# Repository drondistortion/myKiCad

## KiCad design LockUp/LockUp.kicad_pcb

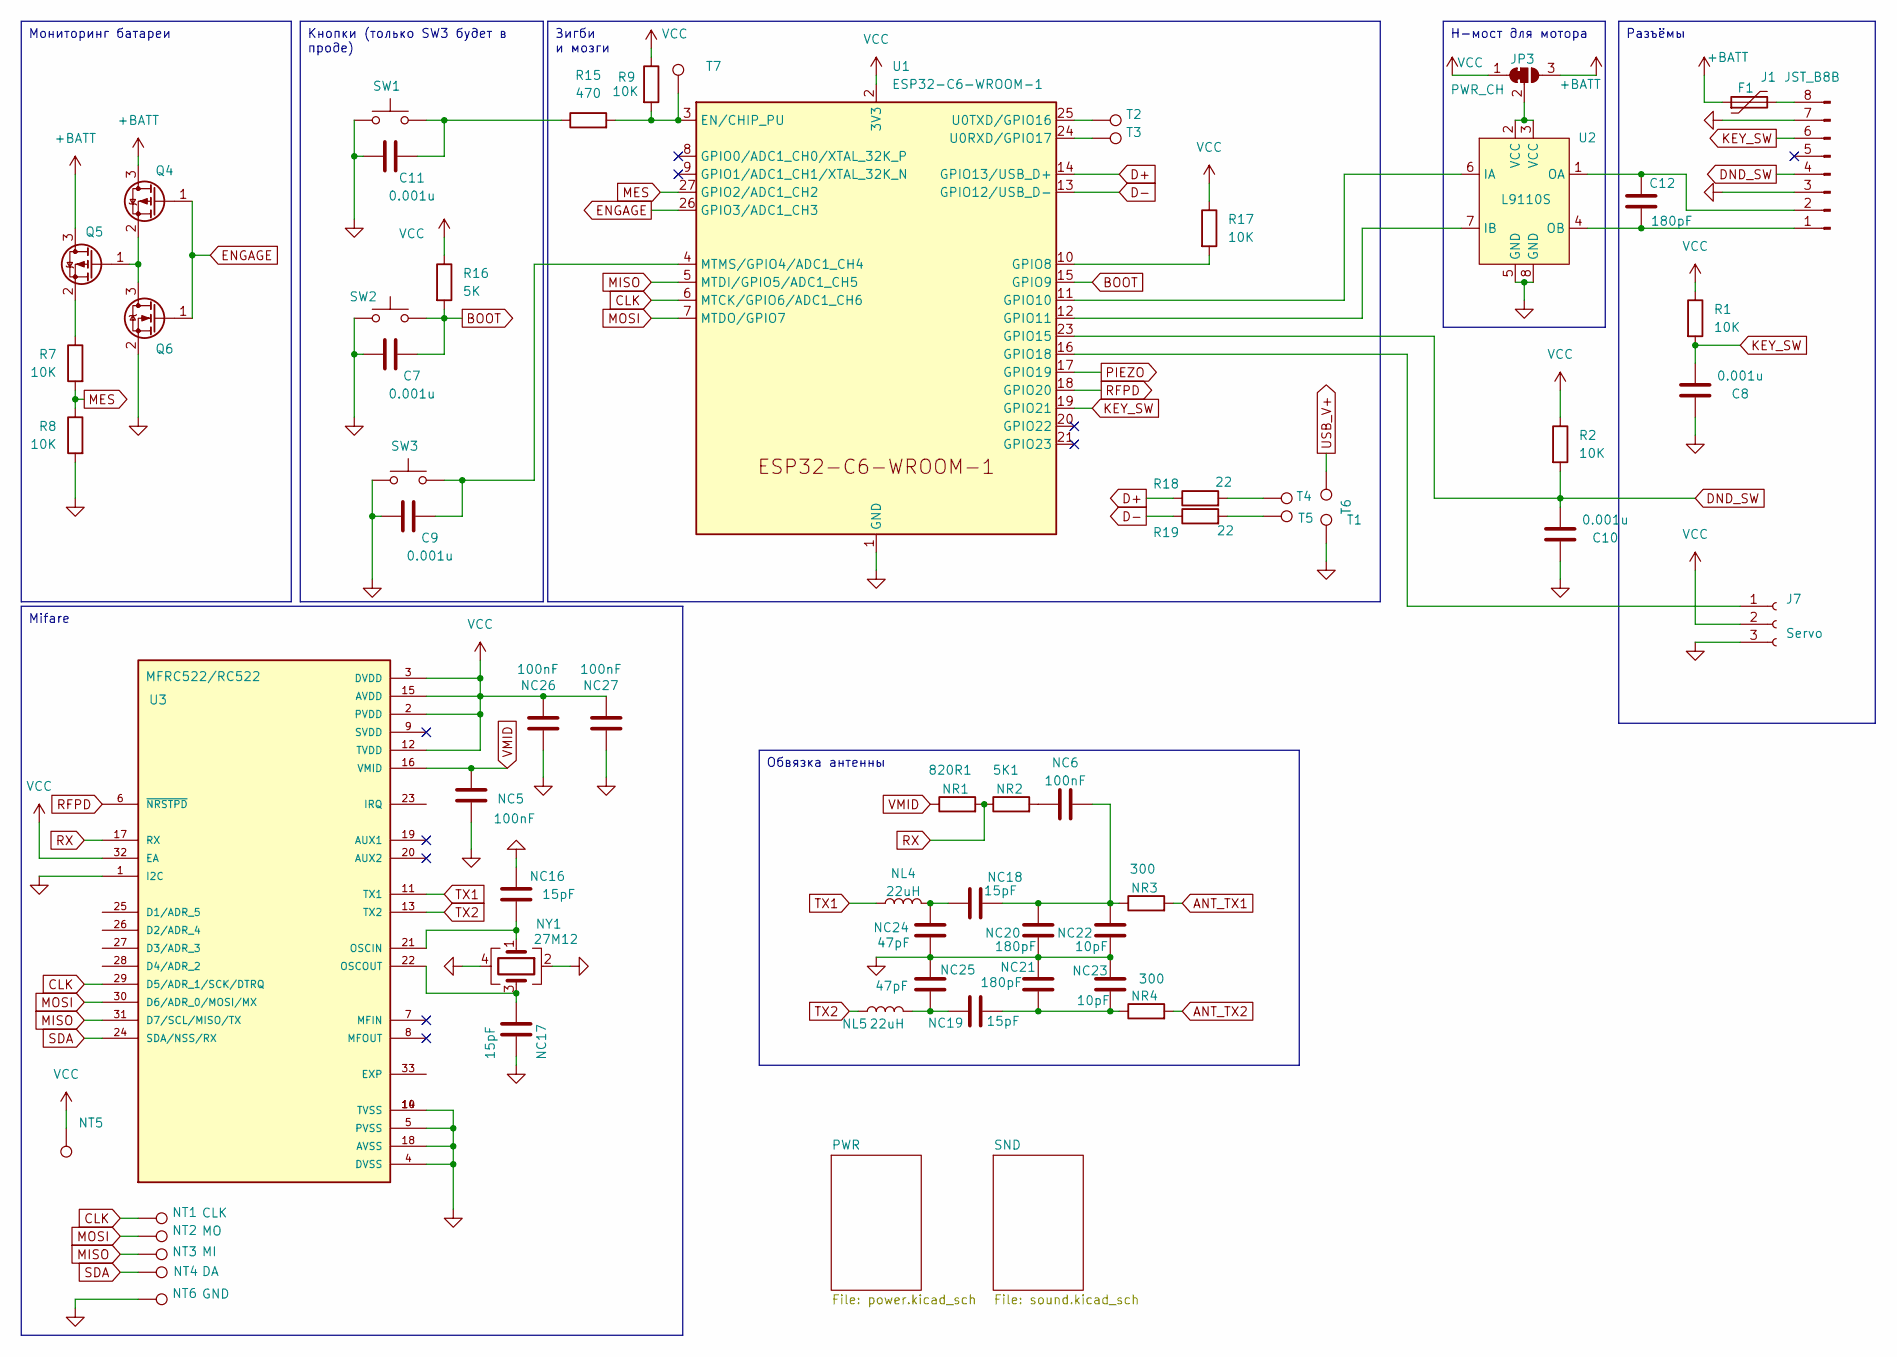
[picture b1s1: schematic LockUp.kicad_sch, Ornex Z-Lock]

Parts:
C7, C8, C9, C10, C11: 0.001u; C_0805_2012Metric_Pad1.18x1.45mm_HandSolder
C12: 180pF; C_0805_2012Metric_Pad1.18x1.45mm_HandSolder
F1: Polyfuse; Fuse_1206_3216Metric_Pad1.42x1.75mm_HandSolder
J1: JST_B8B; JST_PH_B8B-PH-SM4-TB_1x08-1MP_P2.00mm_Vertical
J7: Servo; Molex_PicoBlade_53398-0371_1x03-1MP_P1.25mm_Vertical
JP3: PWR_CH; SolderJumper-3_P1.3mm_Bridged12_RoundedPad1.0x1.5mm
NC5, NC6, NC26, NC27: 100nF; C_0805_2012Metric_Pad1.18x1.45mm_HandSolder
NC16, NC17, NC18, NC19: 15pF; C_0805_2012Metric_Pad1.18x1.45mm_HandSolder
NC20, NC21: 180pF; C_0805_2012Metric_Pad1.18x1.45mm_HandSolder
NC22, NC23: 10pF; C_0805_2012Metric_Pad1.18x1.45mm_HandSolder
NC24, NC25: 47pF; C_0805_2012Metric_Pad1.18x1.45mm_HandSolder
NL4, NL5: 22uH; L_0805_2012Metric_Pad1.15x1.40mm_HandSolder
NR1: 820R1; R_0805_2012Metric_Pad1.20x1.40mm_HandSolder
NR2: 5K1; R_0805_2012Metric_Pad1.20x1.40mm_HandSolder
NR3, NR4: 300; R_0805_2012Metric_Pad1.20x1.40mm_HandSolder
NT1: CLK; TestPoint_Pad_1.0x1.0mm
NT2: MO; TestPoint_Pad_1.0x1.0mm
NT3: MI; TestPoint_Pad_1.0x1.0mm
NT4: DA; TestPoint_Pad_1.0x1.0mm
NT5: 3V3; TestPoint_Pad_1.0x1.0mm
NT6: GND; TestPoint_Pad_1.0x1.0mm
NY1: 27M12; Crystal_SMD_3225-4Pin_3.2x2.5mm_HandSoldering
Q4, Q5: Si2323; SOT-23
Q6: AO3400A; SOT-23
R1, R2, R7, R8, R9, R17: 10K; R_0805_2012Metric_Pad1.20x1.40mm_HandSolder
R15: 470; R_0805_2012Metric_Pad1.20x1.40mm_HandSolder
R16: 5K; R_0805_2012Metric_Pad1.20x1.40mm_HandSolder
R18, R19: 22; R_0805_2012Metric_Pad1.20x1.40mm_HandSolder
SW1: RST; SW_Push_1P1T_XKB_TS-1187A
SW2: BOOT; SW_Push_1P1T_XKB_TS-1187A
SW3: NT_RST; SW_Push_1P1T_XKB_TS-1187A
T1: GND; TestPoint_THTPad_D0.6mm_Drill0.3mm
T2: TX; TestPoint_Pad_D1.0mm
T3: RX; TestPoint_Pad_D1.0mm
T4: D+; TestPoint_THTPad_D0.6mm_Drill0.3mm
T5: D-; TestPoint_THTPad_D0.6mm_Drill0.3mm
T6: VCC; TestPoint_THTPad_D0.6mm_Drill0.3mm
T7: RES; TestPoint_Pad_D1.0mm
U1: ESP32-C6-WROOM-1
U2: L9110S; SOP-8_3.9x4.9mm_P1.27mm
U3: MFRC522/RC522; HVQFN-32-1EP_5x5mm_P0.5mm_EP3.1x3.1mm; PARTREV 3.9

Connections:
+BATT: F1.1, JP3.3 (B), Q4.3 (D), Q5.3 (D); also elsewhere on the board
ANT_TX1: NR3.2
ANT_TX2: NR4.2
BOOT: C7.2, R16.2, SW2.2, U1.15 (GPIO9)
CLK: NT1.1, U1.6 (MTCK/GPIO6/ADC1_CH6), U3.29 (D5/ADR_1/SCK/DTRQ)
D+: R18.1, U1.14 (GPIO13/USB_D+)
D-: R19.1, U1.13 (GPIO12/USB_D-)
DND_SW: C10.2, J1.4, R2.2, U1.23 (GPIO15)
ENGAGE: Q4.1 (G), Q6.1 (G), U1.26 (GPIO3/ADC1_CH3)
GND: C7.1, C8.1, C9.1, C10.1, C11.1, J1.3, J1.7, J7.3, NC5.2, NC16.2, NC17.2, NC20.2, NC21.1, NC22.2, NC23.1, NC24.2, NC25.1, NC26.1, NC27.2, NT6.1, NY1.2, NY1.4, Q6.2 (S), R8.2, SW1.1, SW2.1, SW3.1, T1.1, U1.1 (GND), U1.28 (GND), U1.29 (GND), U2.5 (GND), U2.8 (GND), U3.1 (I2C), U3.4 (DVSS), U3.5 (PVSS), U3.10 (TVSS), U3.14 (TVSS), U3.18 (AVSS); also elsewhere on the board
KEY_SW: C8.2, J1.6, R1.2, U1.19 (GPIO21)
MES: R7.2, R8.1, U1.27 (GPIO2/ADC1_CH2)
MISO: NT3.1, U1.5 (MTDI/GPIO5/ADC1_CH5), U3.31 (D7/SCL/MISO/TX)
MOSI: NT2.1, U1.7 (MTDO/GPIO7), U3.30 (D6/ADR_0/MOSI/MX)
unnamed: C11.2, R15.1, SW1.2
unnamed: C12.2, J1.1, U2.4 (OB)
unnamed: C12.1, J1.2, U2.1 (OA)
unnamed: F1.2, J1.8
unnamed: J7.1, U1.16 (GPIO18)
unnamed: JP3.2 (C), U2.2 (VCC), U2.3 (VCC)
unnamed: NC6.1, NR2.2
unnamed: NC18.1, NC24.1, NL4.2
unnamed: NC6.2, NC18.2, NC20.1, NC22.1, NR3.1
unnamed: NC19.1, NC25.2, NL5.2
unnamed: NC19.2, NC21.2, NC23.2, NR4.1
unnamed: Q4.2 (S), Q5.1 (G), Q6.3 (D)
unnamed: Q5.2 (S), R7.1
unnamed: R18.2, T4.1
unnamed: R19.2, T5.1
unnamed: R9.2, R15.2, T7.1, U1.3 (EN/CHIP_PU)
unnamed: R17.2, U1.10 (GPIO8)
unnamed: U1.11 (GPIO10), U2.6 (IA)
unnamed: U1.12 (GPIO11), U2.7 (IB)
unnamed: C9.2, SW3.2, U1.4 (MTMS/GPIO4/ADC1_CH4)
unnamed: T3.1, U1.24 (U0RXD/GPIO17)
unnamed: T2.1, U1.25 (U0TXD/GPIO16)
unnamed: NC16.1, NY1.1, U3.21 (OSCIN)
unnamed: NC17.1, NY1.3, U3.22 (OSCOUT)
PIEZO: U1.17 (GPIO19); also elsewhere on the board
RFPD: U1.18 (GPIO20), U3.6 (~NRSTPD)
RX: NR1.2, NR2.1, U3.17 (RX)
SDA: NT4.1, U3.24 (SDA/NSS/RX)
TX1: NL4.1, U3.11 (TX1)
TX2: NL5.1, U3.13 (TX2)
USB_V+: T6.1; also elsewhere on the board
VCC: J7.2, JP3.1 (A), NC26.2, NC27.1, NT5.1, R1.1, R2.1, R9.1, R16.1, R17.1, U1.2 (3V3), U3.2 (PVDD), U3.3 (DVDD), U3.12 (TVDD), U3.15 (AVDD), U3.32 (EA); also elsewhere on the board
VMID: NC5.1, NR1.1, U3.16 (VMID)

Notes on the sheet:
Мониторинг батареи
Кнопки (только SW3 будет в проде)
Mifare
Н-мост для мотора
Разъёмы
Обвязка антенны
Зигби и мозги

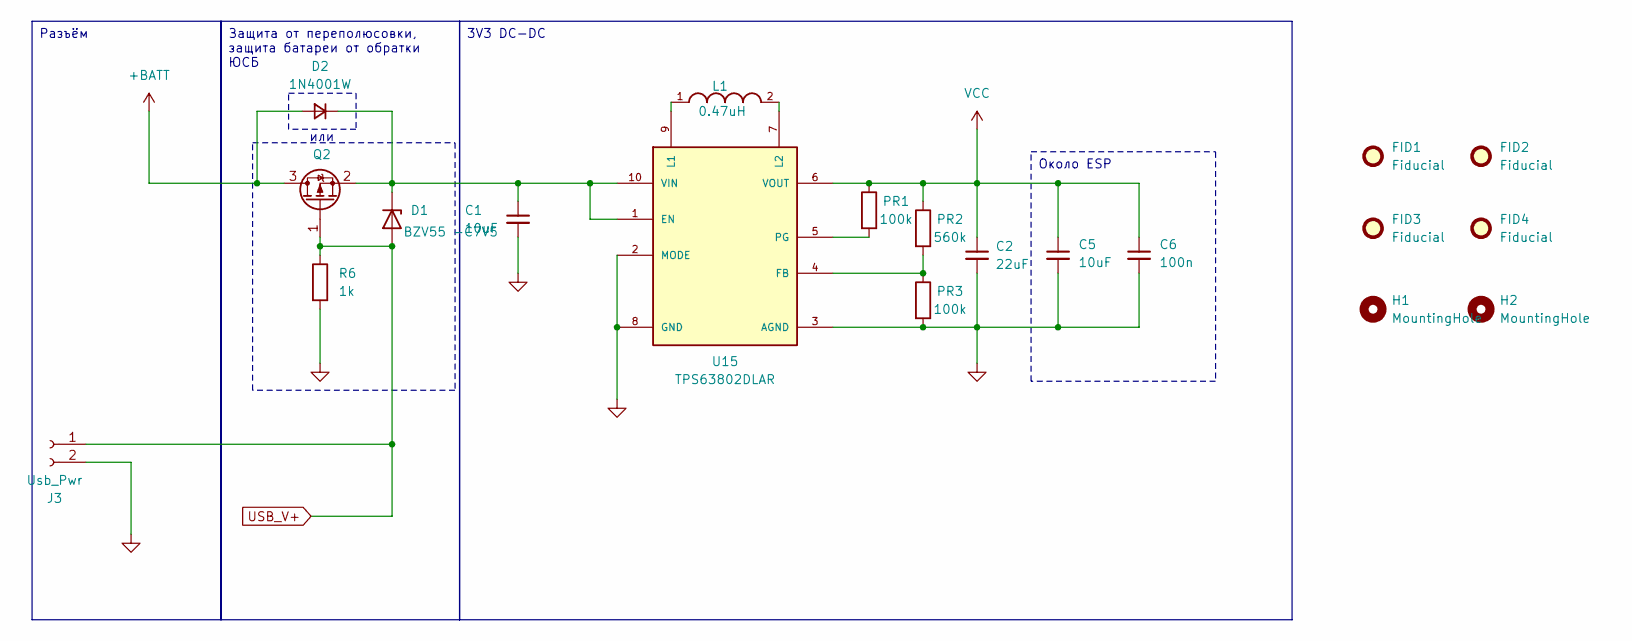
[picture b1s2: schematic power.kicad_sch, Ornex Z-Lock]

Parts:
C1, C5: 10uF; C_0805_2012Metric_Pad1.18x1.45mm_HandSolder; LCSC Part # C19702
C2: 22uF; C_0805_2012Metric_Pad1.18x1.45mm_HandSolder; LCSC Part # C59461
C6: 100n; C_0805_2012Metric_Pad1.18x1.45mm_HandSolder; LCSC Part # C19702
D1: BZV55 -C7V5; D_MiniMELF_Handsoldering
D2: 1N4001W; D_SOD-123F
FID1, FID2, FID3, FID4: Fiducial; Fiducial_0.5mm_Mask1mm
H1, H2: MountingHole; MountingHole_3.2mm_M3_ISO14580
J3: Usb_Pwr; Molex_PicoBlade_53398-0271_1x02-1MP_P1.25mm_Vertical
L1: 0.47uH; INDC2016X120N; LCSC Part # C668312
PR1, PR3: 100k; R_0805_2012Metric_Pad1.20x1.40mm_HandSolder; LCSC Part # C25803
PR2: 560k; R_0805_2012Metric_Pad1.20x1.40mm_HandSolder; LCSC Part # C101109
Q2: Si2323; SOT-23
R6: 1k; R_0805_2012Metric_Pad1.20x1.40mm_HandSolder
U15: TPS63802DLAR; LCSC Part # C2845237

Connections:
+BATT: D2.2 (A), Q2.3 (D); also elsewhere on the board
GND: C1.2, C2.2, C5.2, C6.2, J3.2, PR3.2, R6.2, U15.2 (MODE), U15.3 (AGND), U15.8 (GND); also elsewhere on the board
unnamed: C1.1, D1.1 (K), D2.1 (K), Q2.2 (S), U15.1 (EN), U15.10 (VIN)
unnamed: PR2.2, PR3.1, U15.4 (FB)
unnamed: L1.1, U15.9 (L1)
unnamed: L1.2, U15.7 (L2)
unnamed: PR1.2, U15.5 (PG)
USB_V+: D1.2 (A), J3.1, Q2.1 (G), R6.1; also elsewhere on the board
VCC: C2.1, C5.1, C6.1, PR1.1, PR2.1, U15.6 (VOUT); also elsewhere on the board

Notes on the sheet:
или
Около ESP
Защита от переполюсовки, защита батареи от обратки ЮСБ
Разъём
3V3 DC-DC

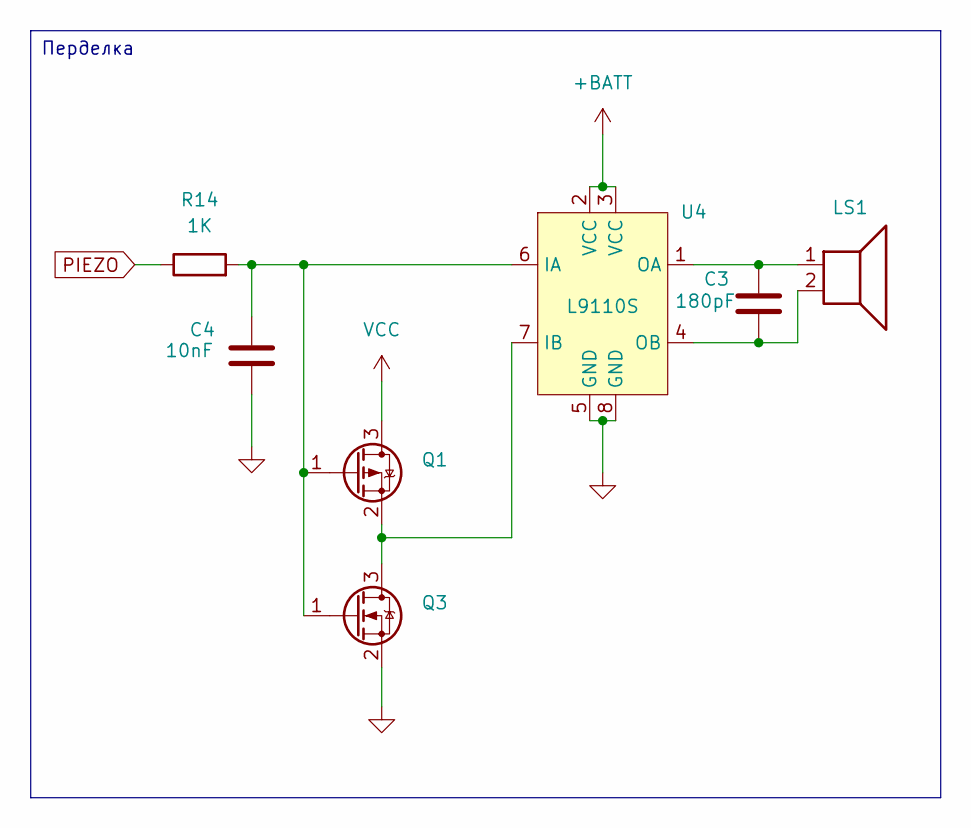
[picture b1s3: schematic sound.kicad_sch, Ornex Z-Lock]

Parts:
C3: 180pF; C_0805_2012Metric_Pad1.18x1.45mm_HandSolder
C4: 10nF; C_0805_2012Metric_Pad1.18x1.45mm_HandSolder
LS1: PKLCS1212E4001; Buzzer_Mallory_AST1240MLQ
Q1: Si2323; SOT-23
Q3: AO3400A; SOT-23
R14: 1K; R_0805_2012Metric_Pad1.20x1.40mm_HandSolder
U4: L9110S; SOP-8_3.9x4.9mm_P1.27mm

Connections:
+BATT: U4.2 (VCC), U4.3 (VCC); also elsewhere on the board
GND: C4.2, Q3.2 (S), U4.5 (GND), U4.8 (GND); also elsewhere on the board
unnamed: C4.1, Q1.1 (G), Q3.1 (G), R14.2, U4.6 (IA)
unnamed: Q1.2 (S), Q3.3 (D), U4.7 (IB)
unnamed: C3.1, LS1.1, U4.1 (OA)
unnamed: C3.2, LS1.2, U4.4 (OB)
PIEZO: R14.1; also elsewhere on the board
VCC: Q1.3 (D); also elsewhere on the board

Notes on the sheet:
Перделка

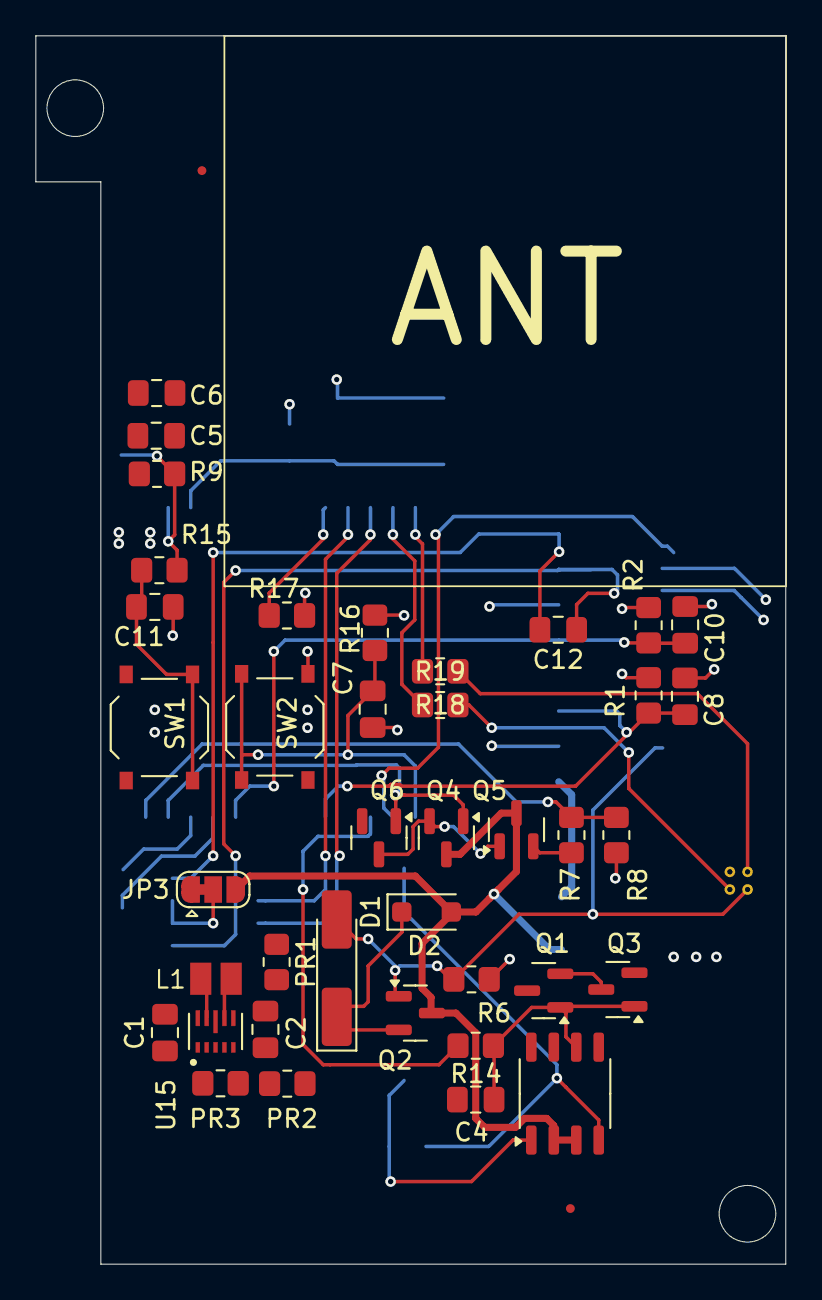
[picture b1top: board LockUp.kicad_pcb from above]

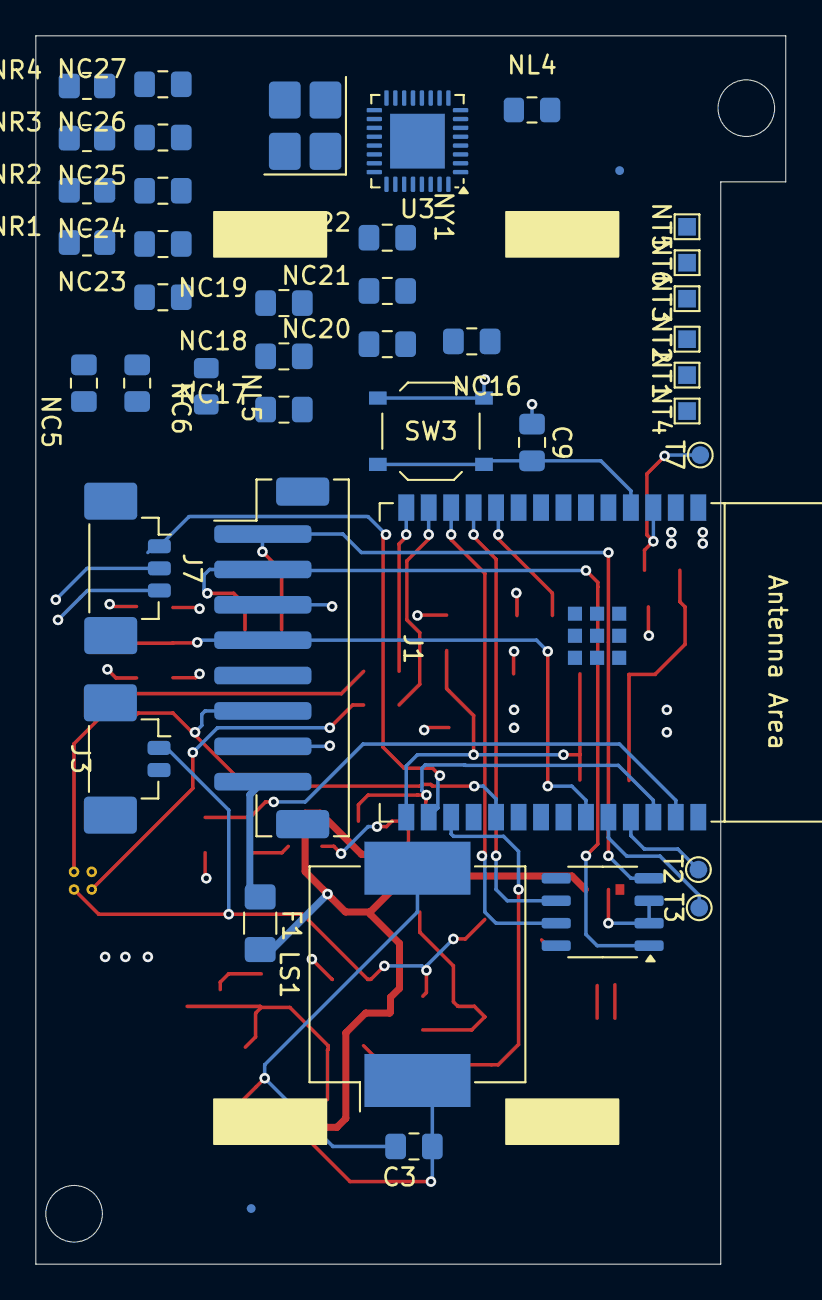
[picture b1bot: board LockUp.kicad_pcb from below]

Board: 4 copper layers, 42.4 x 69.4 mm, 90 parts (43 on the bottom side), 54 nets.

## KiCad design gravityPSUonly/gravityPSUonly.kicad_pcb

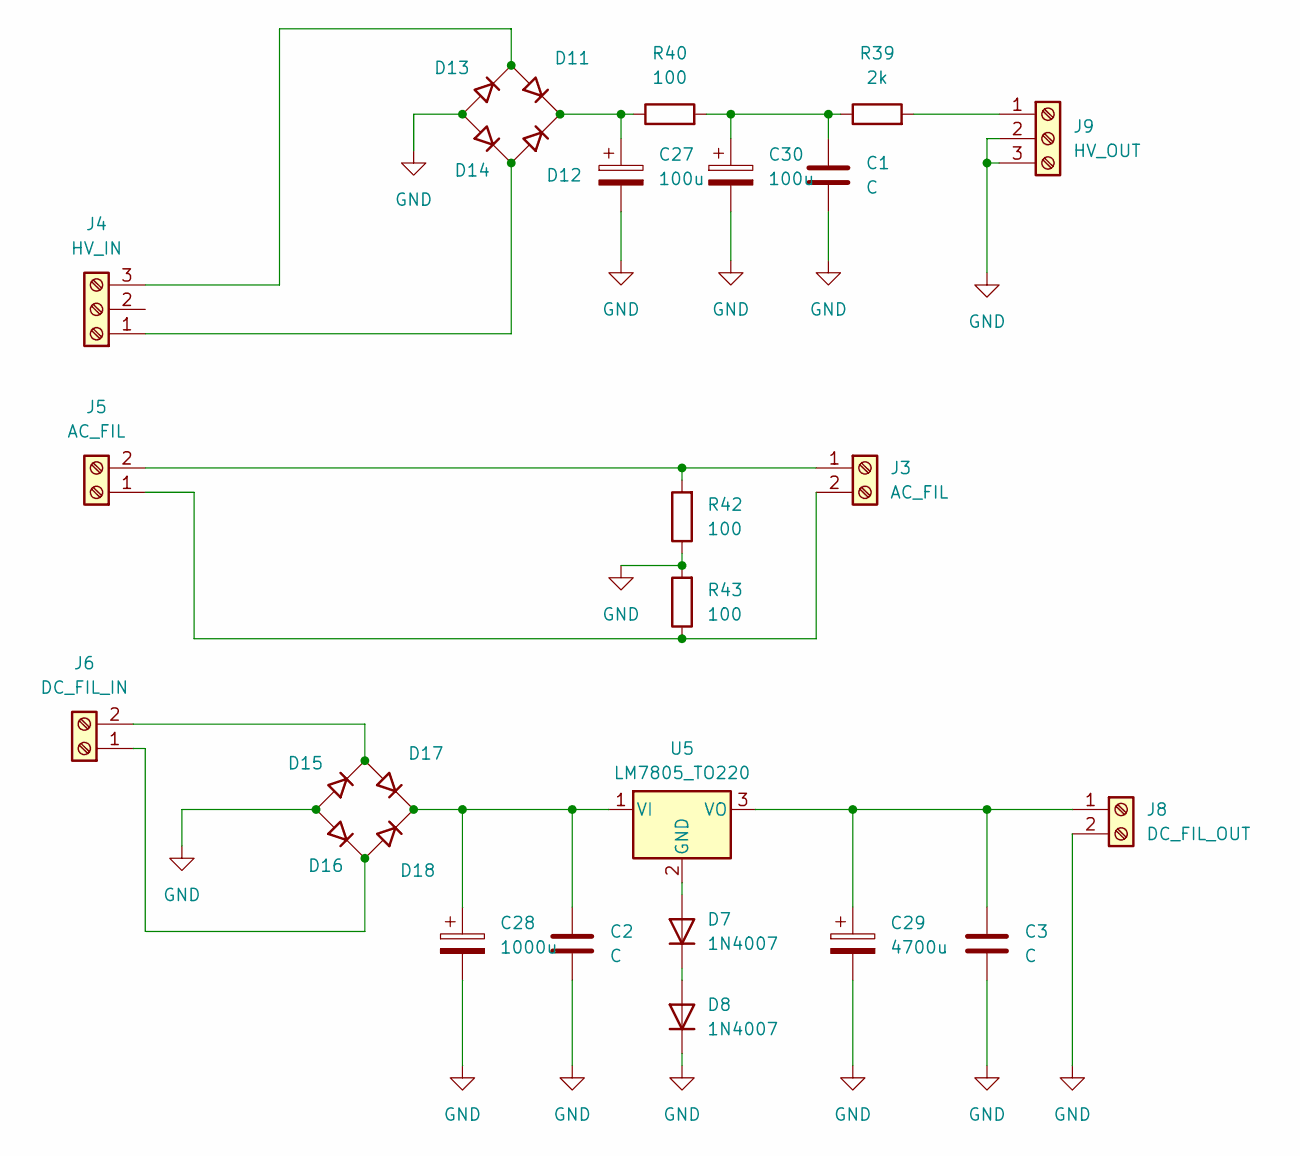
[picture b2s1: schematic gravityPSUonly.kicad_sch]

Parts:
C1, C2, C3: C; C_Rect_L13.5mm_W4.0mm_P10.00mm_FKS3_FKP3_MKS4
C27, C30: 100u; CP_Radial_D18.0mm_P7.50mm
C28: 1000u; CP_Radial_D12.5mm_P5.00mm
C29: 4700u; CP_Radial_D12.5mm_P5.00mm
D7, D8: 1N4007; D_DO-41_SOD81_P10.16mm_Horizontal
D11, D12, D13, D14, D15, D16, D17, D18: D_45deg; D_DO-41_SOD81_P10.16mm_Horizontal
J3, J5: AC_FIL; TerminalBlock_bornier-2_P5.08mm
J4: HV_IN; TerminalBlock_bornier-3_P5.08mm
J6: DC_FIL_IN; TerminalBlock_bornier-2_P5.08mm
J8: DC_FIL_OUT; TerminalBlock_bornier-2_P5.08mm
J9: HV_OUT; TerminalBlock_bornier-3_P5.08mm
R39: 2k; R_Axial_DIN0614_L14.3mm_D5.7mm_P20.32mm_Horizontal
R40: 100; R_Axial_DIN0614_L14.3mm_D5.7mm_P20.32mm_Horizontal
R42, R43: 100; R_Axial_DIN0309_L9.0mm_D3.2mm_P12.70mm_Horizontal
U5: LM7805_TO220; TO-220-3_Vertical

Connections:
GND: C1.2, C2.2, C3.2, C27.2, C28.2, C29.2, C30.2, D8.1 (K), D13.2 (A), D14.2 (A), D15.2 (A), D16.2 (A), J8.2, J9.2, J9.3, R42.1, R43.2
unnamed: C1.1, C30.1, R39.1, R40.2
unnamed: D7.2 (A), U5.2 (GND)
unnamed: D7.1 (K), D8.2 (A)
unnamed: D11.2 (A), D13.1 (K), J4.3
unnamed: C27.1, D11.1 (K), D12.1 (K), R40.1
unnamed: D12.2 (A), D14.1 (K), J4.1
unnamed: D15.1 (K), D17.2 (A), J6.2
unnamed: D16.1 (K), D18.2 (A), J6.1
unnamed: C2.1, C28.1, D17.1 (K), D18.1 (K), U5.1 (VI)
unnamed: J3.1, J5.2, R42.2
unnamed: J3.2, J5.1, R43.1
unnamed: C3.1, C29.1, J8.1, U5.3 (VO)
unnamed: J9.1, R39.2

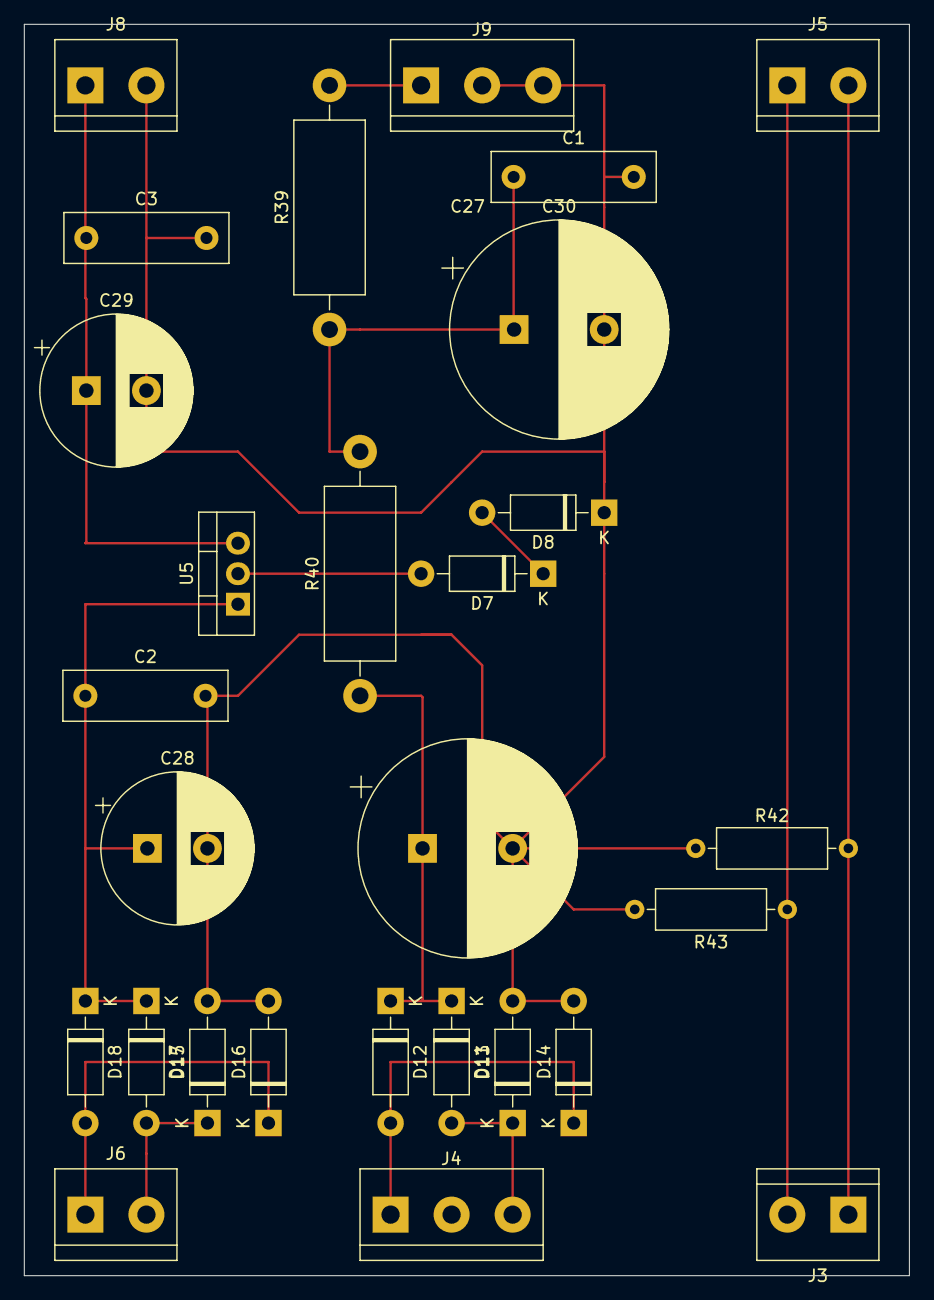
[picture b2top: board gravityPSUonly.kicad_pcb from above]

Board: 2 copper layers, 73.7 x 104.1 mm, 28 parts (0 on the bottom side), 14 nets.

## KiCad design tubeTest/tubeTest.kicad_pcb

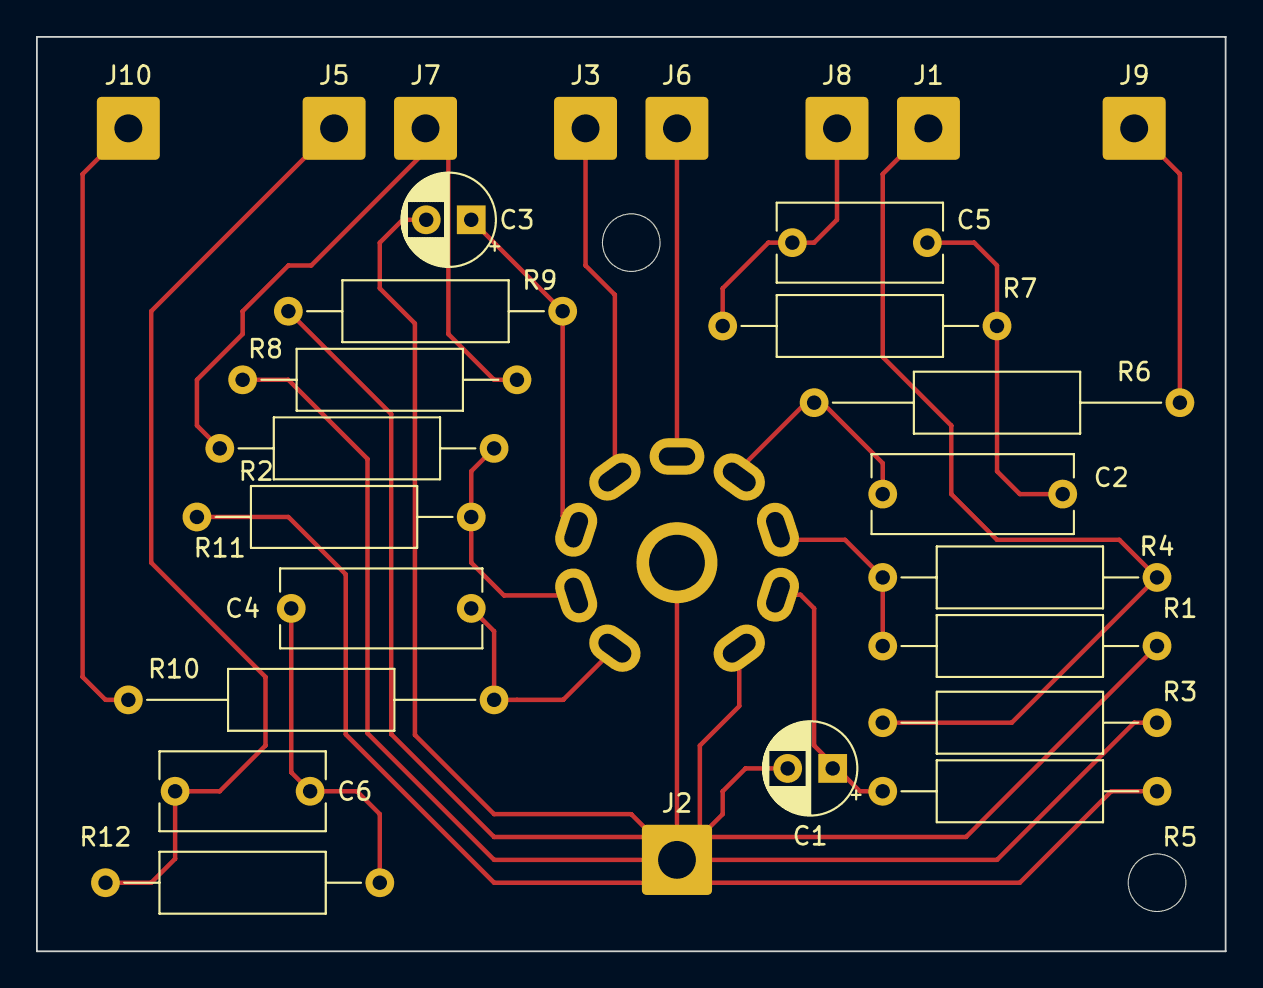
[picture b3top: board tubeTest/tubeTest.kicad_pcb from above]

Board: 2 copper layers, 66.0 x 50.8 mm, 31 parts (1 on the bottom side), 17 nets.

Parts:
C1: 0.1µF; CP_Radial_D5.0mm_P2.50mm
C2, C4: 22n; C_Rect_L11.0mm_W4.2mm_P10.00mm_MKT
C3: 1µF; CP_Radial_D5.0mm_P2.50mm
C5, C6: BRIGHT; C_Rect_L9.0mm_W4.2mm_P7.50mm_MKT
H1, H2, H3: MountingHole; MountingHole_3.2mm_M3
J1: IN_V2; SolderWire-0.75sqmm_1x01_D1.25mm_OD3.5mm
J2: GND; SolderWire-1.5sqmm_1x01_D1.7mm_OD3.9mm
J3, J6: ACFIL; SolderWire-0.75sqmm_1x01_D1.25mm_OD3.5mm
J5: OUT_V1; SolderWire-0.75sqmm_1x01_D1.25mm_OD3.5mm
J7: IN_V1; SolderWire-0.75sqmm_1x01_D1.25mm_OD3.5mm
J8: OUT_V2; SolderWire-0.75sqmm_1x01_D1.25mm_OD3.5mm
J9: HT_V2; SolderWire-0.75sqmm_1x01_D1.25mm_OD3.5mm
J10: HT_V1; SolderWire-0.75sqmm_1x01_D1.25mm_OD3.5mm
R1, R11: DIV; R_Axial_DIN0309_L9.0mm_D3.2mm_P15.24mm_Horizontal
R2, R4: GRID; R_Axial_DIN0309_L9.0mm_D3.2mm_P15.24mm_Horizontal
R3, R8: LEAK; R_Axial_DIN0309_L9.0mm_D3.2mm_P15.24mm_Horizontal
R5, R9: 1.8K; R_Axial_DIN0309_L9.0mm_D3.2mm_P15.24mm_Horizontal
R6, R10: 220K; R_Axial_DIN0309_L9.0mm_D3.2mm_P20.32mm_Horizontal
R7, R12: 470K; R_Axial_DIN0309_L9.0mm_D3.2mm_P15.24mm_Horizontal
U3: ECC83; Valve_ECC-83-2

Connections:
+3V0: J6.1, U3.5 (F1)
-3V3: J3.1, U3.4 (F1)
GND: C1.2, C3.2, J2.1, R1.1, R3.2, R5.2, R8.1, R9.2, R11.1, U3.9 (F2)
unnamed: C1.1, R5.1, U3.8 (K)
unnamed: C2.1, R6.2, U3.6 (A)
unnamed: C2.2, C5.1, R7.1
unnamed: C3.1, R9.1, U3.3 (K)
unnamed: C4.1, R10.2, U3.1 (A)
unnamed: C4.2, C6.1, R12.1
unnamed: J1.1, R3.1, R4.1
unnamed: C6.2, J5.1, R12.2
unnamed: J7.1, R2.1, R8.2
unnamed: C5.2, J8.1, R7.2
unnamed: J9.1, R6.1
unnamed: J10.1, R10.1
unnamed: R1.2, R4.2, U3.7 (G)
unnamed: R2.2, R11.2, U3.2 (G)

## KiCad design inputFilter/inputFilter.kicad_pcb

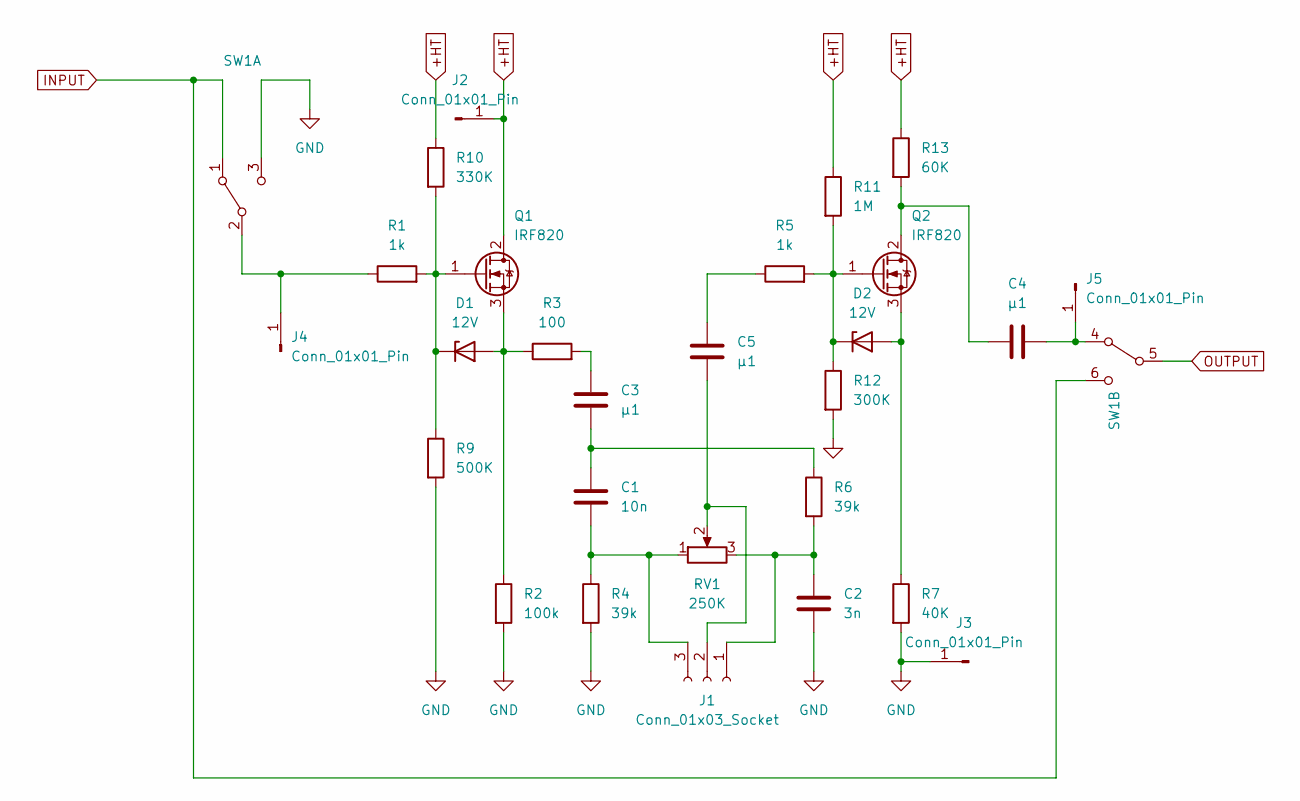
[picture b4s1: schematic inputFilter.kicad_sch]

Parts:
C1: 10n; C_Disc_D12.5mm_W5.0mm_P7.50mm
C2: 3n; C_Disc_D12.5mm_W5.0mm_P7.50mm
C3, C4, C5: µ1; C_Disc_D12.5mm_W5.0mm_P7.50mm
D1, D2: 12V; D_T-1_P5.08mm_Horizontal
J1: Conn_01x03_Socket; SolderWire-0.1sqmm_1x03_P3.6mm_D0.4mm_OD1mm
J2, J3, J4, J5: Conn_01x01_Pin; SolderWire-0.1sqmm_1x01_D0.4mm_OD1mm
Q1, Q2: IRF820; TO-220-3_Vertical
R1, R5: 1k; R_Axial_DIN0414_L11.9mm_D4.5mm_P5.08mm_Vertical
R2: 100k; R_Axial_DIN0414_L11.9mm_D4.5mm_P5.08mm_Vertical
R3: 100; R_Axial_DIN0414_L11.9mm_D4.5mm_P5.08mm_Vertical
R4, R6: 39k; R_Axial_DIN0414_L11.9mm_D4.5mm_P5.08mm_Vertical
R7: 40K; R_Axial_DIN0414_L11.9mm_D4.5mm_P5.08mm_Vertical
R9: 500K; R_Axial_DIN0414_L11.9mm_D4.5mm_P5.08mm_Vertical
R10: 330K; R_Axial_DIN0414_L11.9mm_D4.5mm_P5.08mm_Vertical
R11: 1M; R_Axial_DIN0414_L11.9mm_D4.5mm_P5.08mm_Vertical
R12: 300K; R_Axial_DIN0414_L11.9mm_D4.5mm_P5.08mm_Vertical
R13: 60K; R_Axial_DIN0414_L11.9mm_D4.5mm_P5.08mm_Vertical
RV1: 250K; Potentiometer_Alps_RK09L_Single_Horizontal
SW1: SW_E-Switch_EG2219_DPDT_Angled

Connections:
+HT: J2.1, Q1.2 (D), R10.1, R11.1, R13.1
GND: C2.1, J3.1, R2.2, R4.2, R7.2, R9.2, R12.2
unnamed: C1.2, C3.1, R6.1
unnamed: C3.2, R3.2
unnamed: C5.2, R5.1
unnamed: D1.2 (A), Q1.3 (S), R2.1, R3.1
unnamed: D1.1 (K), Q1.1 (G), R1.2, R9.1, R10.2
unnamed: D2.2 (A), Q2.3 (S), R7.1
unnamed: D2.1 (K), Q2.1 (G), R5.2, R11.2, R12.1
unnamed: C2.2, J1.1, R6.2, RV1.3
unnamed: C5.1, J1.2, RV1.2
unnamed: C1.1, J1.3, R4.1, RV1.1
unnamed: J4.1, R1.1
unnamed: C4.1, J5.1, SW1.4 (A)
unnamed: C4.2, Q2.2 (D), R13.2
unnamed: SW1.1 (A), SW1.6 (C)

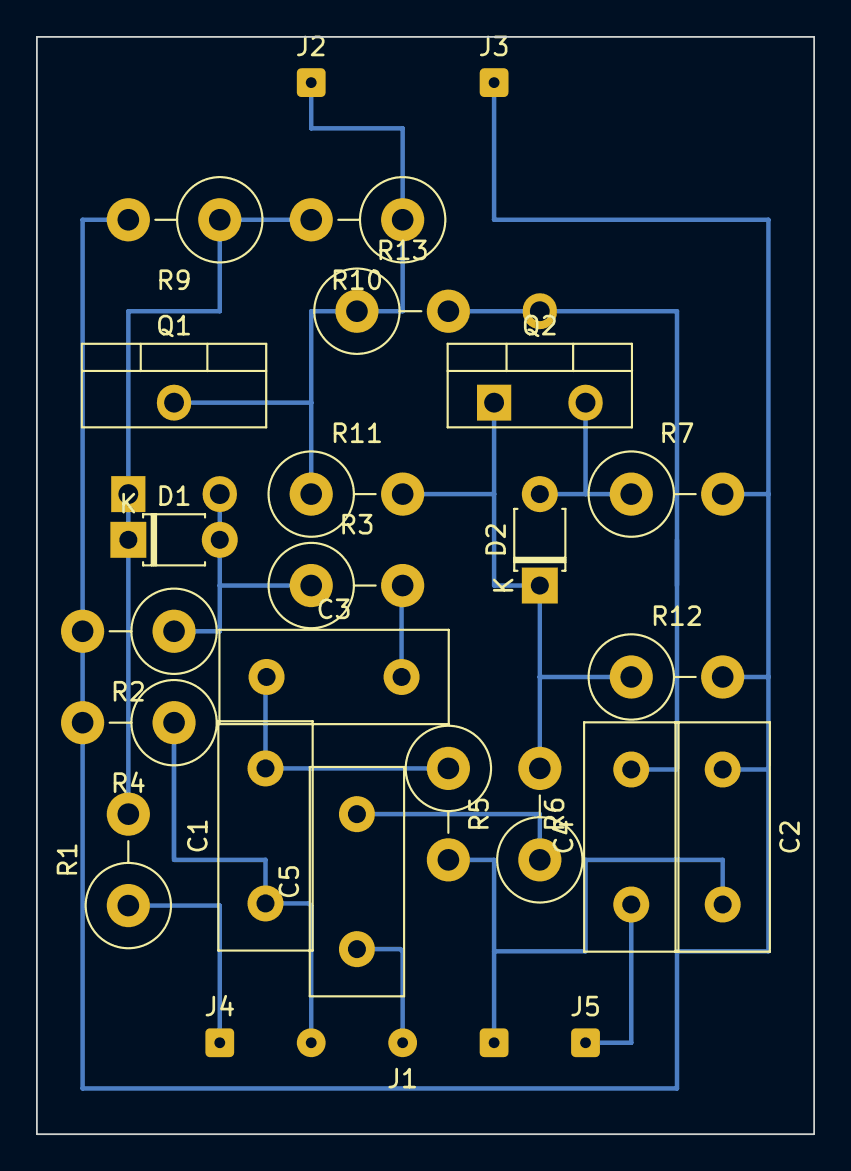
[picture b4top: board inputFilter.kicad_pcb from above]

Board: 2 copper layers, 43.2 x 61.0 mm, 26 parts (0 on the bottom side), 15 nets.

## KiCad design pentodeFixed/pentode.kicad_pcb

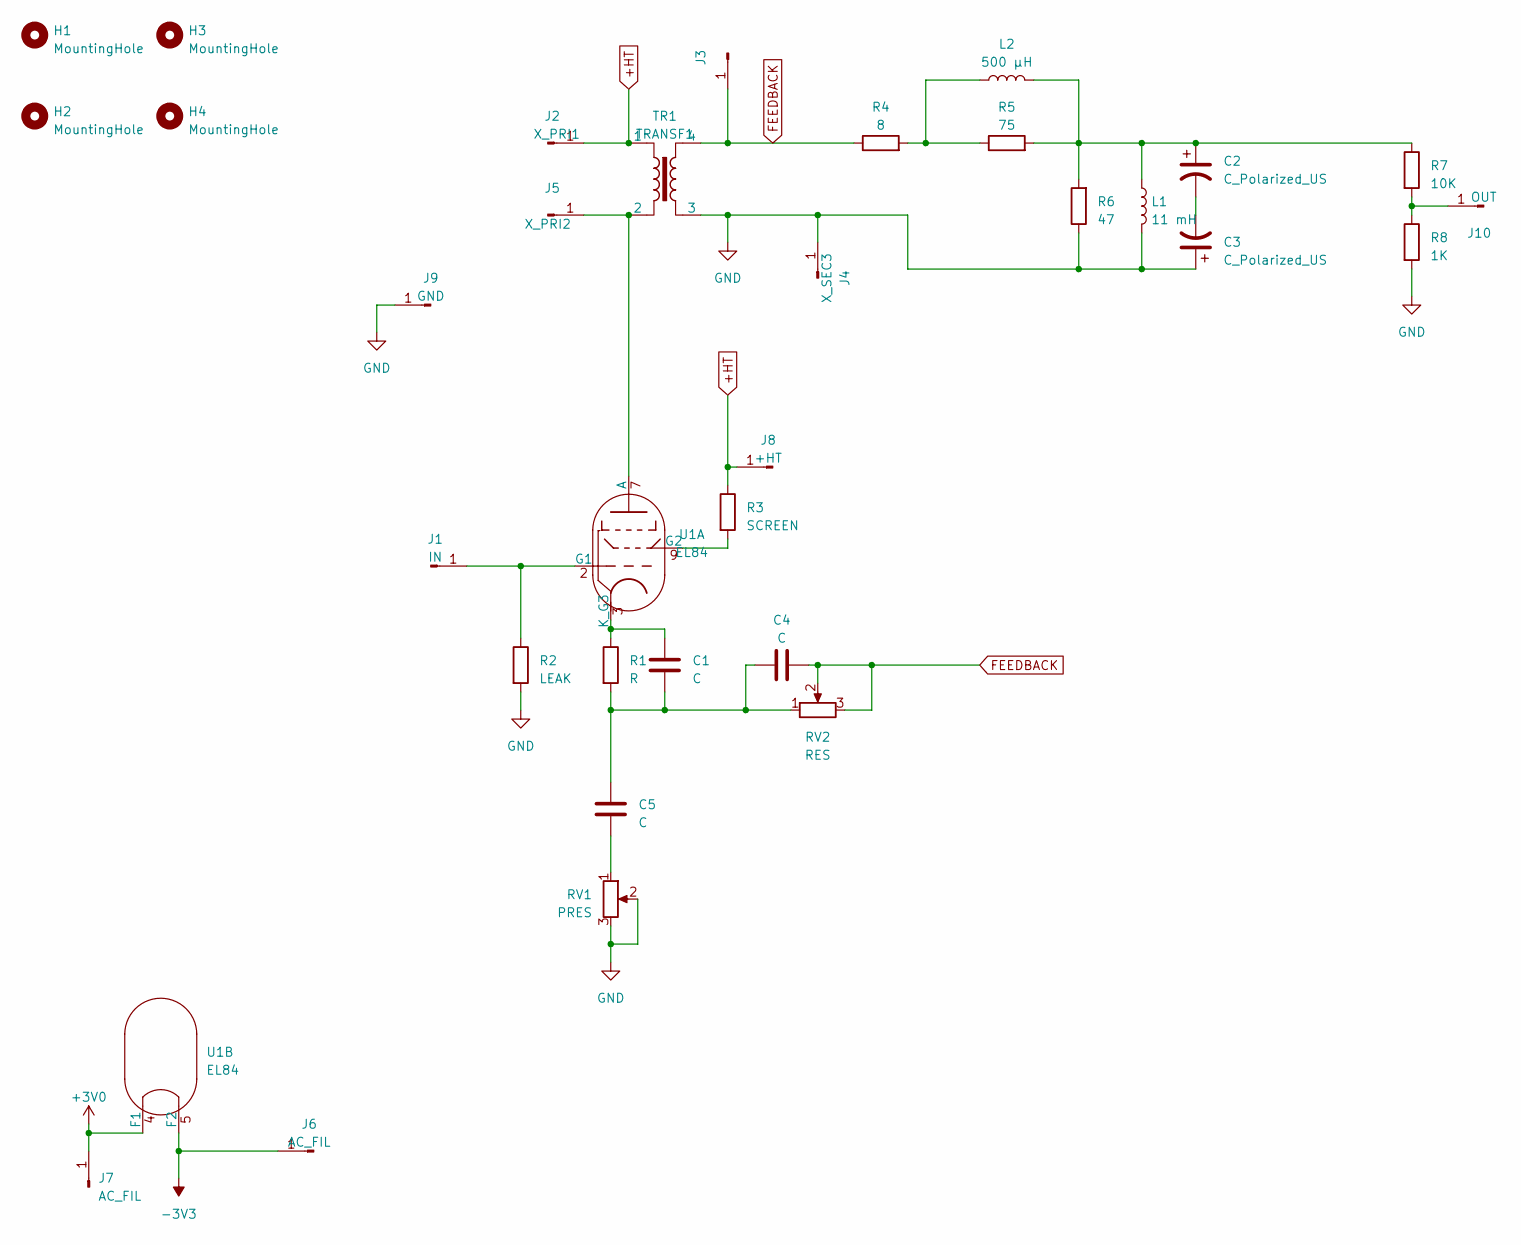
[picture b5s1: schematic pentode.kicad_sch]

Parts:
C1: C; CP_Radial_D5.0mm_P2.50mm
C2, C3: C_Polarized_US; CP_Radial_D14.0mm_P7.50mm
C4, C5: C; C_Rect_L7.2mm_W3.0mm_P5.00mm_FKS2_FKP2_MKS2_MKP2
H1, H2, H3, H4: MountingHole; MountingHole_3.2mm_M3
J1: IN; SolderWire-0.75sqmm_1x01_D1.25mm_OD3.5mm
J2: X_PRI1; SolderWire-0.75sqmm_1x01_D1.25mm_OD3.5mm
J3: X_SEC4; SolderWire-0.75sqmm_1x01_D1.25mm_OD3.5mm
J4: X_SEC3; SolderWire-0.75sqmm_1x01_D1.25mm_OD3.5mm
J5: X_PRI2; SolderWire-0.75sqmm_1x01_D1.25mm_OD3.5mm
J6, J7: AC_FIL; SolderWire-0.75sqmm_1x01_D1.25mm_OD3.5mm
J8: +HT; SolderWire-0.75sqmm_1x01_D1.25mm_OD3.5mm
J9: GND; SolderWire-0.75sqmm_1x01_D1.25mm_OD3.5mm
J10: OUT; SolderWire-0.75sqmm_1x01_D1.25mm_OD3.5mm
L1: 11 mH; L_Toroid_Horizontal_D25.4mm_P22.90mm_Vishay_TJ5_BigPads
L2: 500 µH; L_Axial_L26.0mm_D9.0mm_P30.48mm_Horizontal_Fastron_77A
R1: R; R_Axial_DIN0309_L9.0mm_D3.2mm_P15.24mm_Horizontal
R2: LEAK; R_Axial_DIN0309_L9.0mm_D3.2mm_P15.24mm_Horizontal
R3: SCREEN; R_Axial_DIN0309_L9.0mm_D3.2mm_P15.24mm_Horizontal
R4: 8; R_Axial_Power_L20.0mm_W6.4mm_P25.40mm
R5: 75; R_Axial_Power_L20.0mm_W6.4mm_P25.40mm
R6: 47; R_Axial_Power_L20.0mm_W6.4mm_P25.40mm
R7: 10K; R_Axial_DIN0207_L6.3mm_D2.5mm_P10.16mm_Horizontal
R8: 1K; R_Axial_DIN0207_L6.3mm_D2.5mm_P10.16mm_Horizontal
RV1: PRES; Potentiometer_Pads_Only
RV2: RES; Potentiometer_Pads_Only
TR1: TRANSF1; Transformer_DRON
U1: EL84; Valve_EL84

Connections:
+3V0: J7.1, U1.4 (F1)
+HT: J2.1, J8.1, R3.1, TR1.1
-3V3: J6.1, U1.5 (F2)
FEEDBACK: C4.1, J3.1, R4.1, RV2.2, RV2.3, TR1.4
GND: C3.1, J4.1, J9.1, L1.2, R2.2, R6.1, R8.2, RV1.2, RV1.3, TR1.3
unnamed: C1.2, C4.2, C5.1, R1.2, RV2.1
unnamed: C2.1, L1.1, L2.2, R5.2, R6.2, R7.1
unnamed: C2.2, C3.2
unnamed: C5.2, RV1.1
unnamed: J1.1, R2.1, U1.2 (G1)
unnamed: J5.1, TR1.2, U1.7 (A)
unnamed: J10.1, R7.2, R8.1
unnamed: L2.1, R4.2, R5.1
unnamed: R3.2, U1.9 (G2)
unnamed: C1.1, R1.1, U1.3 (K_G3)
